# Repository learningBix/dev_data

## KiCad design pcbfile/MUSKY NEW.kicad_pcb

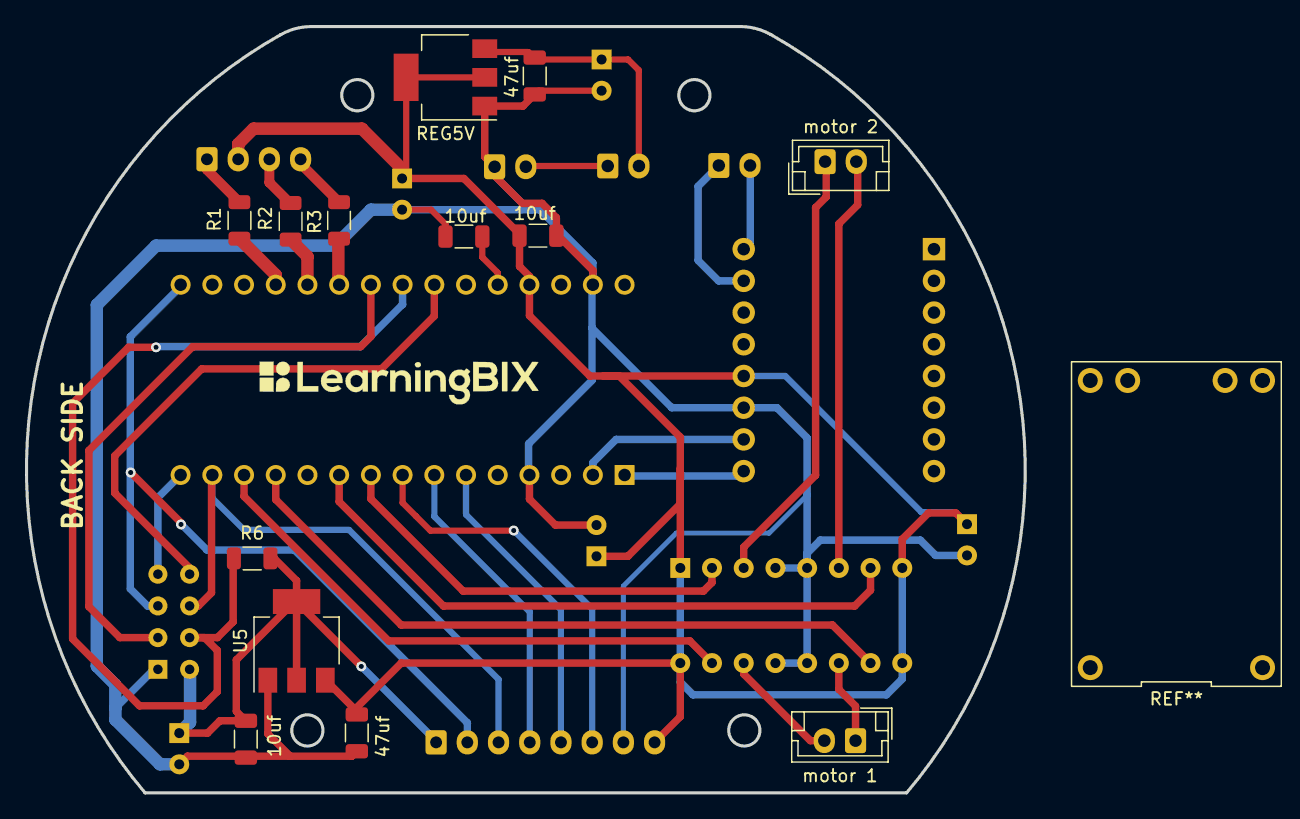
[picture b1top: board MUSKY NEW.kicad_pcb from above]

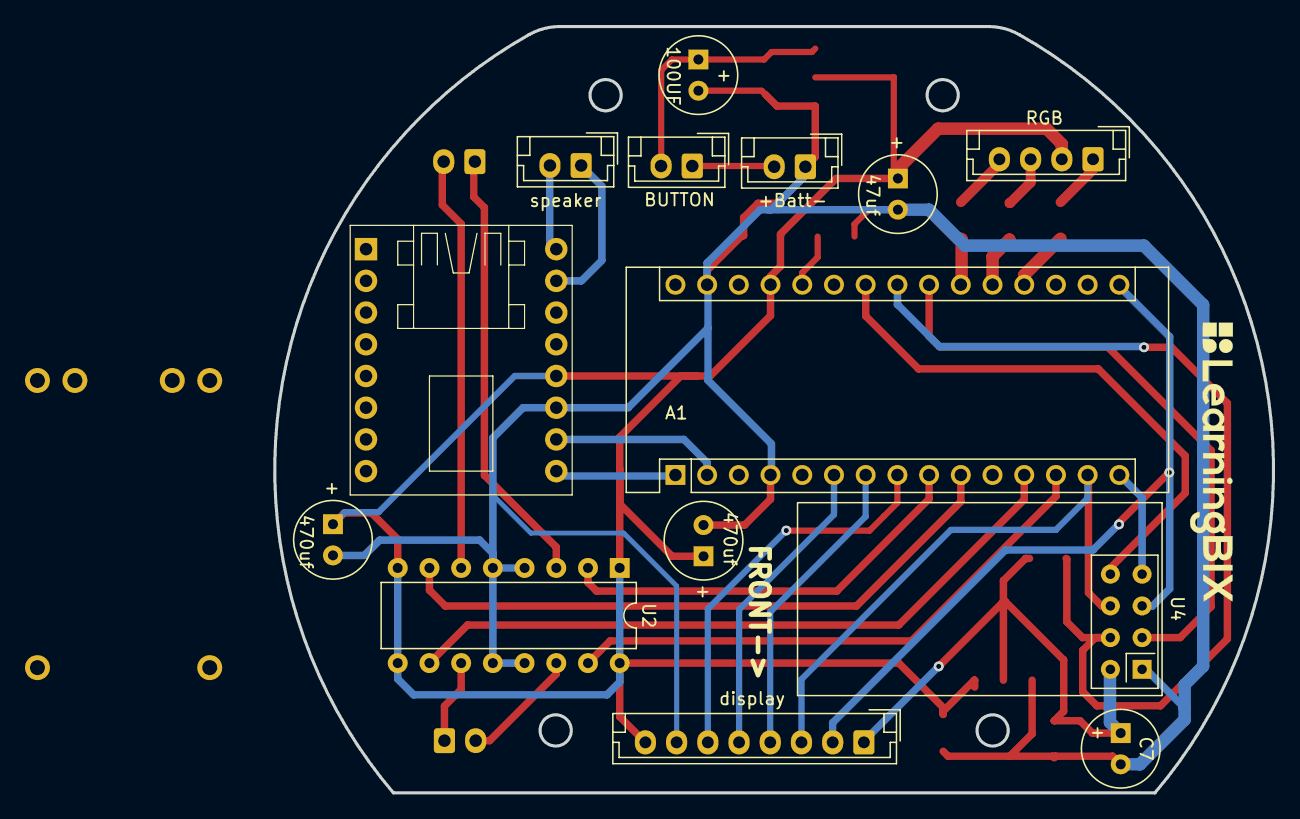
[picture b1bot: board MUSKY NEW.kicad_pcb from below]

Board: 2 copper layers, 80.0 x 61.4 mm, 29 parts (15 on the bottom side), 32 nets.

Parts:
10uf, 10uf#2, 10uf#3, 47uf, 47uf#2: 0.1nF; C_1206_3216Metric
47uf#3, 100UF, 470uf, 470uf#2: 100uF25V; 100uf_25v
+Batt-: LEFT_MOTOR_SOCKET; JST_EH_B2B-EH-A_1x02_P2.50mm_Vertical
A1: Arduino_Nano_Every; Arduino_Nano
BUTTON: LEFT_MOTOR_SOCKET; JST_EH_B2B-EH-A_1x02_P2.50mm_Vertical
C7: 100uF25V; 100uf_25v
JQ6500-16P: VAL**; JQ6500_2x8_P2.54mm
R1, R2, R3: 220E; R_1206_3216Metric
R6: 10K; R_1206_3216Metric
REG5V: AMS1117-3.3; SOT-223-3_TabPin2
RGB: LED_RAGB; JST_EH_B4B-EH-A_1x04_P2.50mm_Vertical
Ref**: logo_mid; logo_medium
Ref**#2: logo_mid; logo_medium
U2: L293D; DIP-16_W7.62mm
U4: NRF24L01_Breakout; nRF24L01_Breakout
U5: AMS1117-3.3; SOT-223-3_TabPin2
display: JST_EH_B8B-EH-A_1x08_P2.50mm_Vertical
motor 1: RIGHT_MOTOR_SOCKET; JST_EH_B2B-EH-A_1x02_P2.50mm_Vertical
motor 2: LEFT_MOTOR_SOCKET; JST_EH_B2B-EH-A_1x02_P2.50mm_Vertical
speaker: LEFT_MOTOR_SOCKET; JST_EH_B2B-EH-A_1x02_P2.50mm_Vertical

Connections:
/3V3+: 10uf#3.1, C7.1, R6.2, U4.2, U5.2, display.1
/5V+: 10uf.1, 47uf.1, 47uf#3.1, 470uf.1, 470uf#2.1, A1.27, JQ6500-16P.12, REG5V.2, RGB.2, U2.1, U2.8, U2.9, U2.16, U5.3, display.8
/5V-: 10uf.2, 10uf#2.2, 10uf#3.2, 47uf.2, 47uf#2.2, 47uf#3.2, 100UF.2, 470uf.2, 470uf#2.2, +Batt-.1, A1.4, A1.29, C7.2, JQ6500-16P.11, REG5V.1, U2.4, U2.5, U2.12, U2.13, U4.1, U5.1, display.7
/LEFT_MOTOR_1_DRIV: U2.3, motor 2.1
/LEFT_MOTOR_1_SIG: A1.9, U2.2
/LEFT_MOTOR_2_DRIV: U2.6, motor 2.2
/LEFT_MOTOR_2_SIG: A1.10, U2.7
/NRF_CE: A1.22, U4.3
/NRF_CS: A1.23, R6.1, U4.4
/NRF_IRQ: A1.24, U4.8
/NRF_MISO: A1.15, U4.7
/NRF_MOSI: A1.14, U4.6, display.3
/NRF_SCK: A1.16, U4.5, display.2
/RIGHT_MOTOR_1_DRIV: U2.11, motor 1.1
/RIGHT_MOTOR_1_SIG: A1.12, U2.10
/RIGHT_MOTOR_2_DRIV: U2.14, motor 1.2
/RIGHT_MOTOR_2_SIG: A1.13, U2.15
A0: A1.7, display.4
unnamed: A1.19, R1.2
unnamed: A1.20, R2.2
unnamed: A1.21, R3.2
unnamed: 10uf#2.1, A1.26
unnamed: R1.1, RGB.1
unnamed: R2.1, RGB.3
unnamed: R3.1, RGB.4
batt+: 47uf#2.1, 100UF.1, +Batt-.2, BUTTON.1, BUTTON.2, REG5V.3
cs: A1.8, display.6
rst: A1.6, display.5
rx: A1.1, JQ6500-16P.9
spk+: JQ6500-16P.16, speaker.2
spk-: JQ6500-16P.15, speaker.1
tx: A1.2, JQ6500-16P.10

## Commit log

2024-11-09 first
